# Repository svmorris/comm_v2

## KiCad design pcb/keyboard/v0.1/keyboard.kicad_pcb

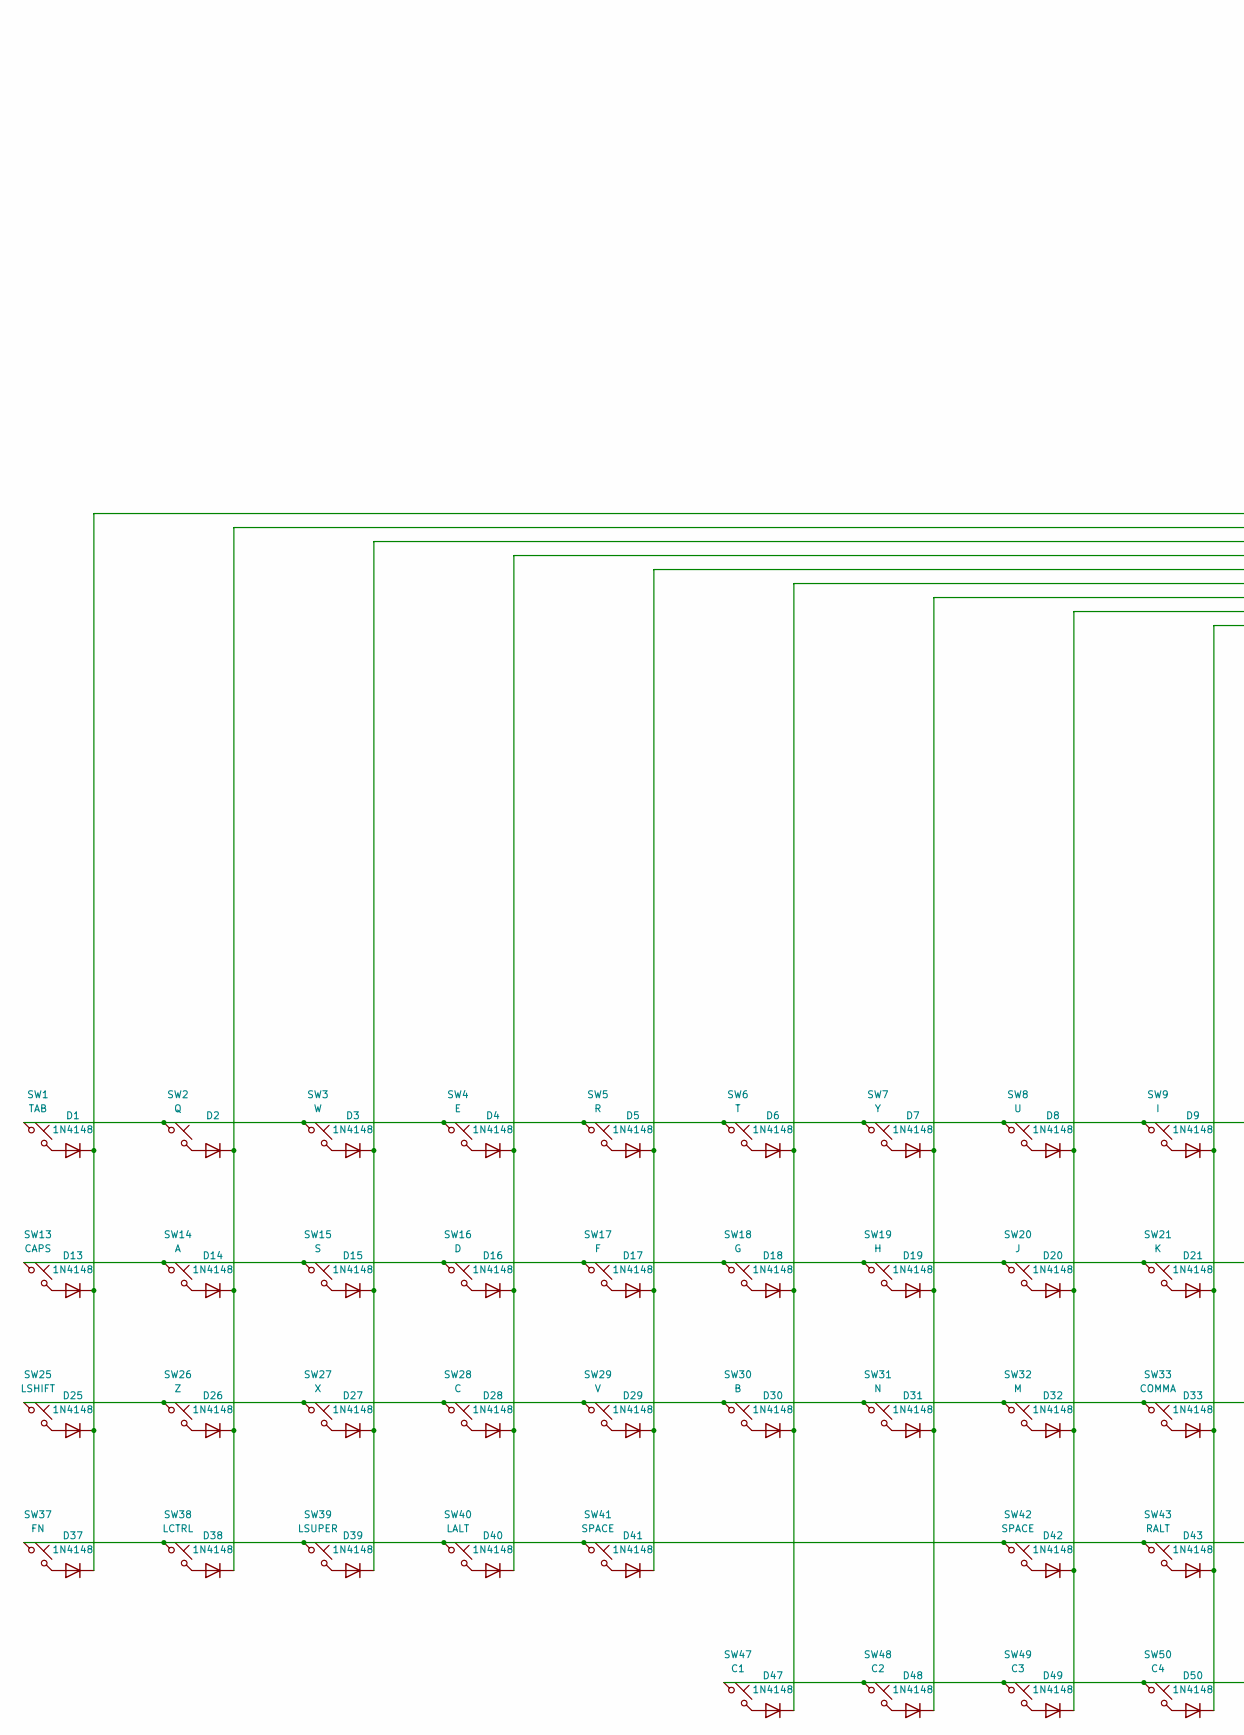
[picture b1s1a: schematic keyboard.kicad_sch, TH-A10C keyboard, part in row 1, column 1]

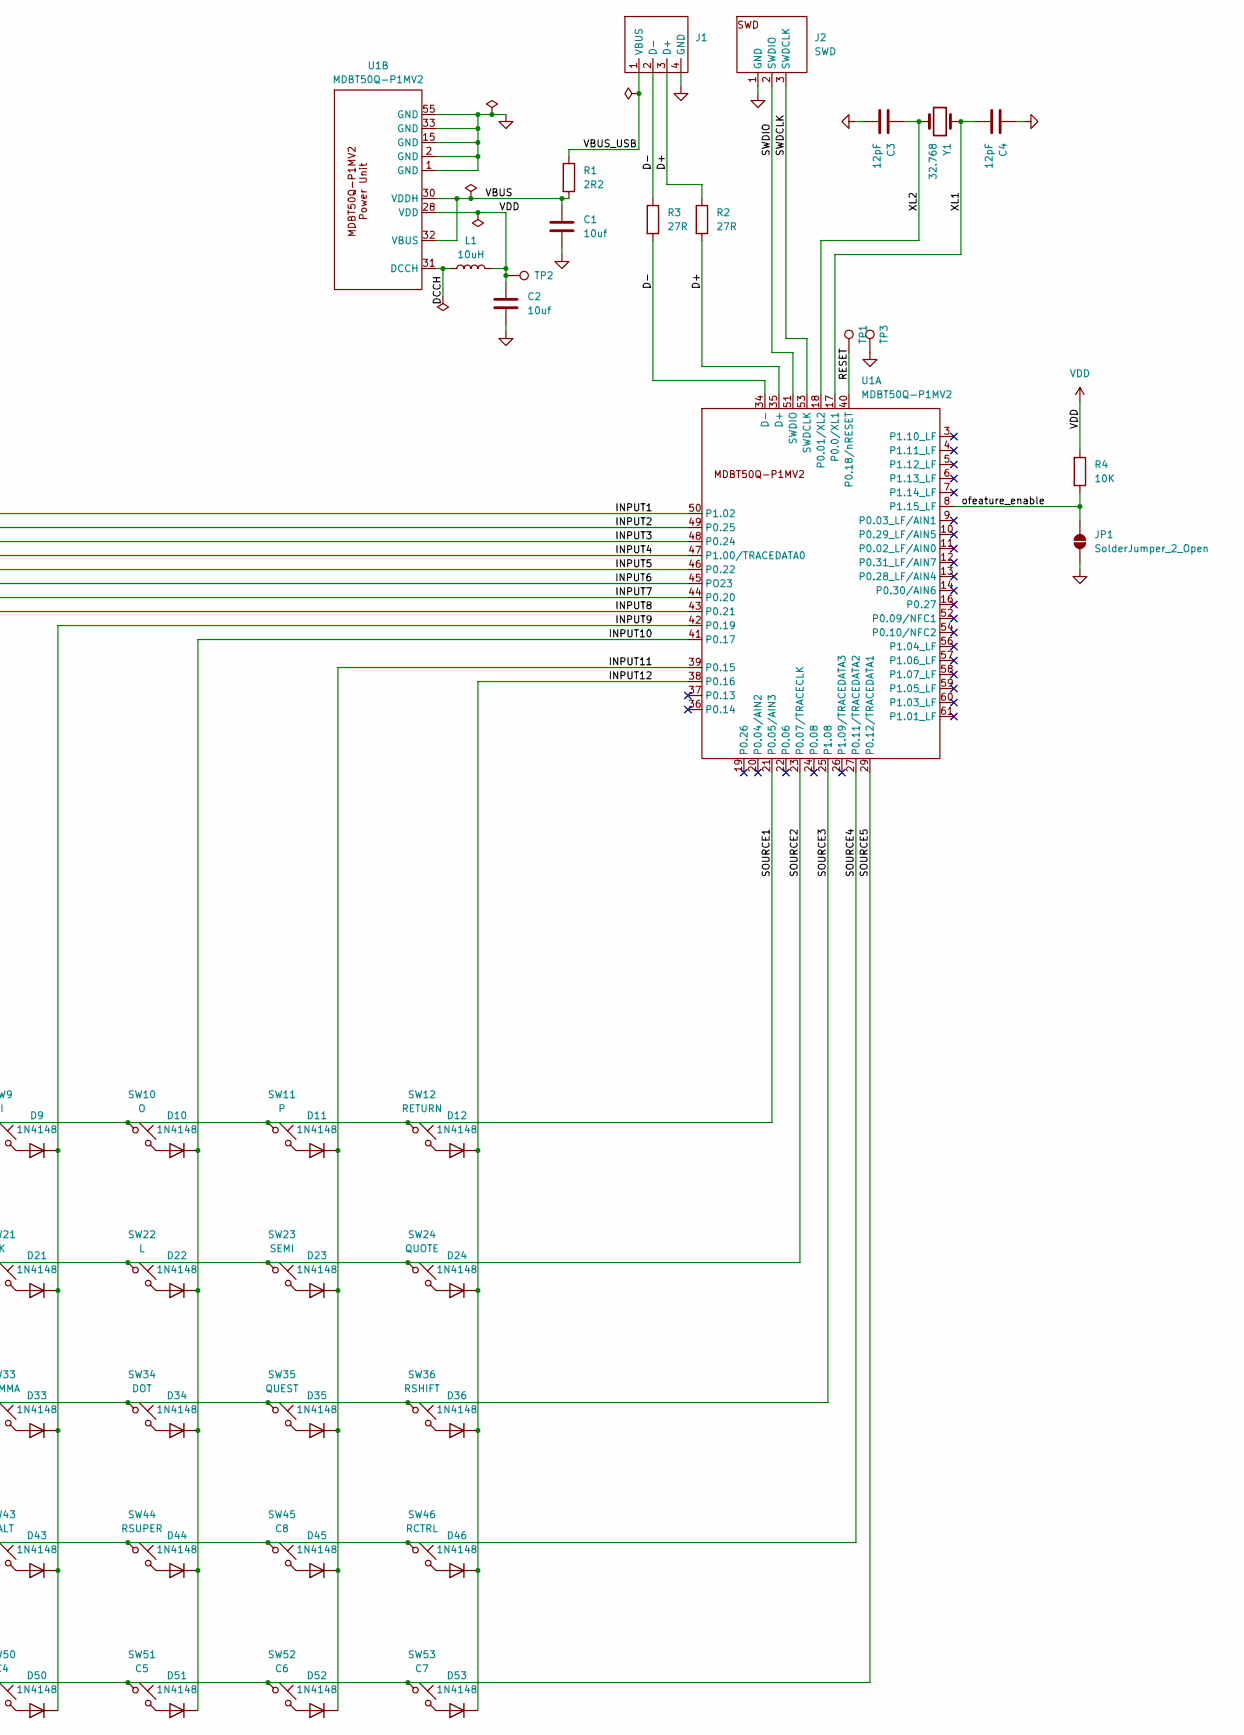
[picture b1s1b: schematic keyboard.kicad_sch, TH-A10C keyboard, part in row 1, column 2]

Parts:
C1, C2: 10uf; C_0805_2012Metric; Mfr. Part no. CL21B106KOQNNNE; LCSC Part no. C95841
C3, C4: 12pF; C_0603_1608Metric; Mfr. Part no. CL10C120JB8NNNC; LCSC Part no. C38523
D1, D2, D3, D4, D5, D6, D7, D8, D9, D10, D11, D12, D13, D14, D15, D16, D17, D18, D19, D20, D21, D22, D23, D24, D25, D26, D27, D28, D29, D30, D31, D32, D33, D34, D35, D36, D37, D38, D39, D40, D41, D42, D43, D44, D45, D46, D47, D48, D49, D50, D51, D52, D53: 1N4148; D_SOD-523; Mfr. Part no. CD4148WTP; LCSC Part no. C30584800
J1: USB2.0; th_pogo_pins_4
J2: SWD; th_pogo_pins_3
JP1: SolderJumper_2_Open; SolderJumper-2_P1.3mm_Open_TrianglePad1.0x1.5mm
L1: 10uH; L_0603_1608Metric; Mfr. Part no SLM1608100MIT; LCSC Part no C2831366
R1: 2R2; R_0603_1608Metric; Mfr. part no. FRC0603F2R20TS; LCSC part no. C2907006
R2, R3: 27R; R_0603_1608Metric; Mfr. part no. 0603WAF270JT5E; LCSC part no. C25190
R4: 10K; R_0603_1608Metric; Mfr. Part no. RC0603FR-0710KL; LCSC Part no. C98220
SW1: TAB; tact_switch_4.5x4.5_PTS647; Mfr. Part no. PTS647SM50SMTR2LFS; LCSC Part no. C2689518
SW2: Q; tact_switch_4.5x4.5_PTS647; Mfr. Part no. PTS647SM50SMTR2LFS; LCSC Part no. C2689518
SW3: W; tact_switch_4.5x4.5_PTS647; Mfr. Part no. PTS647SM50SMTR2LFS; LCSC Part no. C2689518
SW4: E; tact_switch_4.5x4.5_PTS647; Mfr. Part no. PTS647SM50SMTR2LFS; LCSC Part no. C2689518
SW5: R; tact_switch_4.5x4.5_PTS647; Mfr. Part no. PTS647SM50SMTR2LFS; LCSC Part no. C2689518
SW6: T; tact_switch_4.5x4.5_PTS647; Mfr. Part no. PTS647SM50SMTR2LFS; LCSC Part no. C2689518
SW7: Y; tact_switch_4.5x4.5_PTS647; Mfr. Part no. PTS647SM50SMTR2LFS; LCSC Part no. C2689518
SW8: U; tact_switch_4.5x4.5_PTS647; Mfr. Part no. PTS647SM50SMTR2LFS; LCSC Part no. C2689518
SW9: I; tact_switch_4.5x4.5_PTS647; Mfr. Part no. PTS647SM50SMTR2LFS; LCSC Part no. C2689518
SW10: O; tact_switch_4.5x4.5_PTS647; Mfr. Part no. PTS647SM50SMTR2LFS; LCSC Part no. C2689518
SW11: P; tact_switch_4.5x4.5_PTS647; Mfr. Part no. PTS647SM50SMTR2LFS; LCSC Part no. C2689518
SW12: RETURN; tact_switch_4.5x4.5_PTS647; Mfr. Part no. PTS647SM50SMTR2LFS; LCSC Part no. C2689518
SW13: CAPS; tact_switch_4.5x4.5_PTS647; Mfr. Part no. PTS647SM50SMTR2LFS; LCSC Part no. C2689518
SW14: A; tact_switch_4.5x4.5_PTS647; Mfr. Part no. PTS647SM50SMTR2LFS; LCSC Part no. C2689518
SW15: S; tact_switch_4.5x4.5_PTS647; Mfr. Part no. PTS647SM50SMTR2LFS; LCSC Part no. C2689518
SW16: D; tact_switch_4.5x4.5_PTS647; Mfr. Part no. PTS647SM50SMTR2LFS; LCSC Part no. C2689518
SW17: F; tact_switch_4.5x4.5_PTS647; Mfr. Part no. PTS647SM50SMTR2LFS; LCSC Part no. C2689518
SW18: G; tact_switch_4.5x4.5_PTS647; Mfr. Part no. PTS647SM50SMTR2LFS; LCSC Part no. C2689518
SW19: H; tact_switch_4.5x4.5_PTS647; Mfr. Part no. PTS647SM50SMTR2LFS; LCSC Part no. C2689518
SW20: J; tact_switch_4.5x4.5_PTS647; Mfr. Part no. PTS647SM50SMTR2LFS; LCSC Part no. C2689518
SW21: K; tact_switch_4.5x4.5_PTS647; Mfr. Part no. PTS647SM50SMTR2LFS; LCSC Part no. C2689518
SW22: L; tact_switch_4.5x4.5_PTS647; Mfr. Part no. PTS647SM50SMTR2LFS; LCSC Part no. C2689518
SW23: SEMI; tact_switch_4.5x4.5_PTS647; Mfr. Part no. PTS647SM50SMTR2LFS; LCSC Part no. C2689518
SW24: QUOTE; tact_switch_4.5x4.5_PTS647; Mfr. Part no. PTS647SM50SMTR2LFS; LCSC Part no. C2689518
SW25: LSHIFT; tact_switch_4.5x4.5_PTS647; Mfr. Part no. PTS647SM50SMTR2LFS; LCSC Part no. C2689518
SW26: Z; tact_switch_4.5x4.5_PTS647; Mfr. Part no. PTS647SM50SMTR2LFS; LCSC Part no. C2689518
SW27: X; tact_switch_4.5x4.5_PTS647; Mfr. Part no. PTS647SM50SMTR2LFS; LCSC Part no. C2689518
SW28: C; tact_switch_4.5x4.5_PTS647; Mfr. Part no. PTS647SM50SMTR2LFS; LCSC Part no. C2689518
SW29: V; tact_switch_4.5x4.5_PTS647; Mfr. Part no. PTS647SM50SMTR2LFS; LCSC Part no. C2689518
SW30: B; tact_switch_4.5x4.5_PTS647; Mfr. Part no. PTS647SM50SMTR2LFS; LCSC Part no. C2689518
SW31: N; tact_switch_4.5x4.5_PTS647; Mfr. Part no. PTS647SM50SMTR2LFS; LCSC Part no. C2689518
SW32: M; tact_switch_4.5x4.5_PTS647; Mfr. Part no. PTS647SM50SMTR2LFS; LCSC Part no. C2689518
SW33: COMMA; tact_switch_4.5x4.5_PTS647; Mfr. Part no. PTS647SM50SMTR2LFS; LCSC Part no. C2689518
SW34: DOT; tact_switch_4.5x4.5_PTS647; Mfr. Part no. PTS647SM50SMTR2LFS; LCSC Part no. C2689518
SW35: QUEST; tact_switch_4.5x4.5_PTS647; Mfr. Part no. PTS647SM50SMTR2LFS; LCSC Part no. C2689518
SW36: RSHIFT; tact_switch_4.5x4.5_PTS647; Mfr. Part no. PTS647SM50SMTR2LFS; LCSC Part no. C2689518
SW37: FN; tact_switch_4.5x4.5_PTS647; Mfr. Part no. PTS647SM50SMTR2LFS; LCSC Part no. C2689518
SW38: LCTRL; tact_switch_4.5x4.5_PTS647; Mfr. Part no. PTS647SM50SMTR2LFS; LCSC Part no. C2689518
SW39: LSUPER; tact_switch_4.5x4.5_PTS647; Mfr. Part no. PTS647SM50SMTR2LFS; LCSC Part no. C2689518
SW40: LALT; tact_switch_4.5x4.5_PTS647; Mfr. Part no. PTS647SM50SMTR2LFS; LCSC Part no. C2689518
SW41, SW42: SPACE; tact_switch_4.5x4.5_PTS647; Mfr. Part no. PTS647SM50SMTR2LFS; LCSC Part no. C2689518
SW43: RALT; tact_switch_4.5x4.5_PTS647; Mfr. Part no. PTS647SM50SMTR2LFS; LCSC Part no. C2689518
SW44: RSUPER; tact_switch_4.5x4.5_PTS647; Mfr. Part no. PTS647SM50SMTR2LFS; LCSC Part no. C2689518
SW45: C8; tact_switch_4.5x4.5_PTS647; Mfr. Part no. PTS647SM50SMTR2LFS; LCSC Part no. C2689518
SW46: RCTRL; tact_switch_4.5x4.5_PTS647; Mfr. Part no. PTS647SM50SMTR2LFS; LCSC Part no. C2689518
SW47: C1; tact_switch_4.5x4.5_PTS647; Mfr. Part no. PTS647SM50SMTR2LFS; LCSC Part no. C2689518
SW48: C2; tact_switch_4.5x4.5_PTS647; Mfr. Part no. PTS647SM50SMTR2LFS; LCSC Part no. C2689518
SW49: C3; tact_switch_4.5x4.5_PTS647; Mfr. Part no. PTS647SM50SMTR2LFS; LCSC Part no. C2689518
SW50: C4; tact_switch_4.5x4.5_PTS647; Mfr. Part no. PTS647SM50SMTR2LFS; LCSC Part no. C2689518
SW51: C5; tact_switch_4.5x4.5_PTS647; Mfr. Part no. PTS647SM50SMTR2LFS; LCSC Part no. C2689518
SW52: C6; tact_switch_4.5x4.5_PTS647; Mfr. Part no. PTS647SM50SMTR2LFS; LCSC Part no. C2689518
SW53: C7; tact_switch_4.5x4.5_PTS647; Mfr. Part no. PTS647SM50SMTR2LFS; LCSC Part no. C2689518
TP1, TP2, TP3: TestPoint; TestPoint_Pad_D2.0mm
U1: MDBT50Q-P1MV2; TH_MDBT50Q-P1MV2; Mfr Part no. MDBT50Q-P1MV2; LCSC Part no. C5119772
Y1: 32.768; Crystal_SMD_3215-2Pin_3.2x1.5mm; Mfr. Part no. Q13FC13500003; LCSC Part no. C99010

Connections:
/D+: J1.3 (D+), R2.1, R2.2, U1.35 (D+)
/D-: J1.2 (D-), R3.1, R3.2, U1.34 (D-)
/DCCH: L1.1, U1.31 (DCCH)
/INPUT1: D1.1 (K), D13.1 (K), D25.1 (K), D37.1 (K), U1.50 (P1.02)
/INPUT2: D2.1 (K), D14.1 (K), D26.1 (K), D38.1 (K), U1.49 (P0.25)
/INPUT3: D3.1 (K), D15.1 (K), D27.1 (K), D39.1 (K), U1.48 (P0.24)
/INPUT4: D4.1 (K), D16.1 (K), D28.1 (K), D40.1 (K), U1.47 (P1.00/TRACEDATA0)
/INPUT5: D5.1 (K), D17.1 (K), D29.1 (K), D41.1 (K), U1.46 (P0.22)
/INPUT6: D6.1 (K), D18.1 (K), D30.1 (K), D47.1 (K), U1.45 (PO23)
/INPUT7: D7.1 (K), D19.1 (K), D31.1 (K), D48.1 (K), U1.44 (P0.20)
/INPUT8: D8.1 (K), D20.1 (K), D32.1 (K), D42.1 (K), D49.1 (K), U1.43 (P0.21)
/INPUT9: D9.1 (K), D21.1 (K), D33.1 (K), D43.1 (K), D50.1 (K), U1.42 (P0.19)
/INPUT10: D10.1 (K), D22.1 (K), D34.1 (K), D44.1 (K), D51.1 (K), U1.41 (P0.17)
/INPUT11: D11.1 (K), D23.1 (K), D35.1 (K), D45.1 (K), D52.1 (K), U1.39 (P0.15)
/INPUT12: D12.1 (K), D24.1 (K), D36.1 (K), D46.1 (K), D53.1 (K), U1.38 (P0.16)
/RESET: TP1.1, U1.40 (P0.18/nRESET)
/SOURCE1: SW1.1, SW2.1, SW3.1, SW4.1, SW5.1, SW6.1, SW7.1, SW8.1, SW9.1, SW10.1, SW11.1, SW12.1, U1.21 (P0.05/AIN3)
/SOURCE2: SW13.1, SW14.1, SW15.1, SW16.1, SW17.1, SW18.1, SW19.1, SW20.1, SW21.1, SW22.1, SW23.1, SW24.1, U1.23 (P0.07/TRACECLK)
/SOURCE3: SW25.1, SW26.1, SW27.1, SW28.1, SW29.1, SW30.1, SW31.1, SW32.1, SW33.1, SW34.1, SW35.1, SW36.1, U1.25 (P1.08)
/SOURCE4: SW37.1, SW38.1, SW39.1, SW40.1, SW41.1, SW42.1, SW43.1, SW44.1, SW45.1, SW46.1, U1.27 (P0.11/TRACEDATA2)
/SOURCE5: SW47.1, SW48.1, SW49.1, SW50.1, SW51.1, SW52.1, SW53.1, U1.29 (P0.12/TRACEDATA1)
/SWDCLK: J2.3 (SWDCLK), U1.53 (SWDCLK)
/SWDIO: J2.2 (SWDIO), U1.51 (SWDIO)
/VBUS: C1.1, R1.2, U1.30 (VDDH), U1.32 (VBUS)
/VBUS_USB: J1.1 (VBUS), R1.1
/XL1: C4.1, U1.17 (P0.0/XL1), Y1.1
/XL2: C3.2, U1.18 (P0.01/XL2), Y1.2
/ofeature_enable: JP1.2 (B), R4.2, U1.8 (P1.15_LF)
GND: C1.2, C2.2, C3.1, C4.2, J1.4 (GND), J2.1 (GND), JP1.1 (A), TP3.1, U1.1 (GND), U1.2 (GND), U1.15 (GND), U1.33 (GND), U1.55 (GND)
unnamed: D1.2 (A), SW1.2
unnamed: D2.2 (A), SW2.2
unnamed: D3.2 (A), SW3.2
unnamed: D4.2 (A), SW4.2
unnamed: D5.2 (A), SW5.2
unnamed: D6.2 (A), SW6.2
unnamed: D7.2 (A), SW7.2
unnamed: D8.2 (A), SW8.2
unnamed: D9.2 (A), SW9.2
unnamed: D10.2 (A), SW10.2
unnamed: D11.2 (A), SW11.2
unnamed: D12.2 (A), SW12.2
unnamed: D13.2 (A), SW13.2
unnamed: D14.2 (A), SW14.2
unnamed: D15.2 (A), SW15.2
unnamed: D16.2 (A), SW16.2
unnamed: D17.2 (A), SW17.2
unnamed: D18.2 (A), SW18.2
unnamed: D19.2 (A), SW19.2
unnamed: D20.2 (A), SW20.2
unnamed: D21.2 (A), SW21.2
unnamed: D22.2 (A), SW22.2
unnamed: D23.2 (A), SW23.2
unnamed: D24.2 (A), SW24.2
unnamed: D25.2 (A), SW25.2
unnamed: D26.2 (A), SW26.2
unnamed: D27.2 (A), SW27.2
unnamed: D28.2 (A), SW28.2
unnamed: D29.2 (A), SW29.2
unnamed: D30.2 (A), SW30.2
unnamed: D31.2 (A), SW31.2
unnamed: D32.2 (A), SW32.2
unnamed: D33.2 (A), SW33.2
unnamed: D34.2 (A), SW34.2
unnamed: D35.2 (A), SW35.2
unnamed: D36.2 (A), SW36.2
unnamed: D37.2 (A), SW37.2
unnamed: D38.2 (A), SW38.2
unnamed: D39.2 (A), SW39.2
unnamed: D40.2 (A), SW40.2
unnamed: D41.2 (A), SW41.2
unnamed: D42.2 (A), SW42.2
unnamed: D43.2 (A), SW43.2
unnamed: D44.2 (A), SW44.2
unnamed: D45.2 (A), SW45.2
unnamed: D46.2 (A), SW46.2
unnamed: D47.2 (A), SW47.2
unnamed: D48.2 (A), SW48.2
unnamed: D49.2 (A), SW49.2
unnamed: D50.2 (A), SW50.2
unnamed: D51.2 (A), SW51.2
unnamed: D52.2 (A), SW52.2
unnamed: D53.2 (A), SW53.2
VDD: C2.1, L1.2, R4.1, TP2.1, U1.28 (VDD)

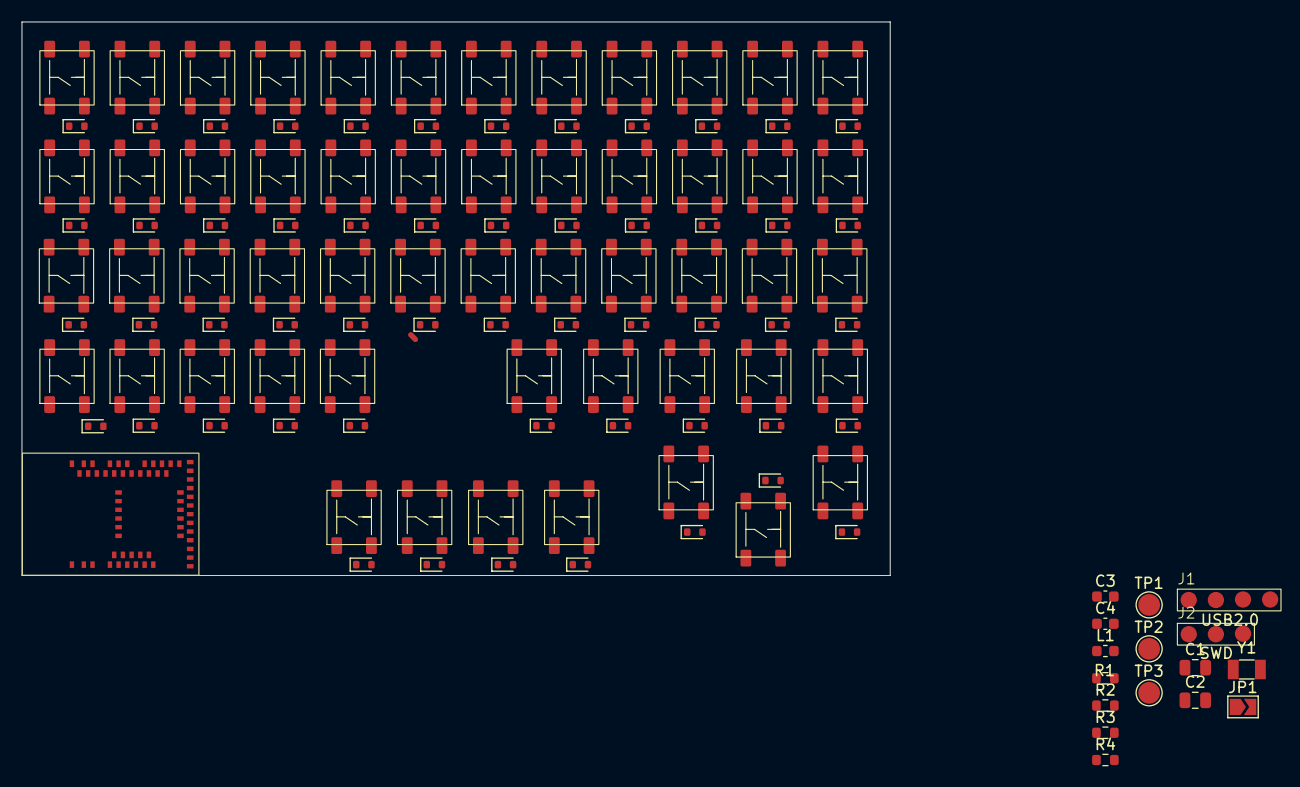
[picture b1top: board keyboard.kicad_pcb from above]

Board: 4 copper layers, 80.0 x 51.0 mm, 123 parts (0 on the bottom side), 83 nets.

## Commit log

2026-02-16 Added zephyr dependency
2026-02-16 Basic USB HID implementation for the keyboard module.
    This commit adds a basic hid keyboard implementation that lines up with
    how the key detection will be done in the code.
2026-02-16 Add keyboard version 0 design files.
    Commit adds the first PCB used for prototyping the keyboard. Named v0
    since this isn't meant to be a functioning keyboard, but rather a board
    with buttons to aid firmware development.
2026-02-17 Quick and dirty keyboard implementation.
    With this commit there is now a functioning keyboard firmware. It can
    do everything a keyboard should, except modifier keys. The current keys
    architecture kinda sucks and should get re-written.
2026-02-18 Finish keyboard v0 design
    This is an early version of the keyboard whose only purpose is to be a
    prototype while I'm working on the firmware for it. Its not to scale, it
    doesn't have an MCU, and its made entirely out of through-hole
    components.
2026-02-20 Clean up keyboard implementation + add mod and fn key.
    The keyboard implementation is now a lot nicer. Its not only more
    efficient, but now has full support for any mod keys.
    Additionally it also includes a custom fn key. This allows for custom
    behaviour defined per key. FN keys can either be part of layer1 where it
    just sends an alternate key, or they can have custom per key functions
    called which are able to do anything.
2026-02-20 Cleaned up some debug messages and usb.c/h functions
2026-02-24 Add initial parts design files
2026-02-26 Rename and update parts
2026-03-02 Switch dp25 -> pin interface
2026-03-06 MCU components complete.
    Only keyboard components and layout to go.
2026-03-07 Found part numbers for button and diode in the keyboard matrix
2026-03-07 Much improved
2026-03-07 Complete keyboard schematic (hopefully)
    Footprints have not been assigned to the keys or the main pcb yet
2026-03-09 Fix incorrect inductor label. 4.7uh -> 10uh
2026-03-10 Labels :)
2026-03-12 Footprints for the two pogo pads
2026-03-12 Footprint for the NRF module!
    Finally I think this means I am done with footprints. Only layout and 3d
    models to go.
2026-03-14 Initial keys layout
    Not sure if this is how we want it yet. Will have to test out without
    the silkscreen key labels if it might give some more space
2026-03-14 Rough layout
2026-03-15 Initial body plan for v3
2026-03-20 New layout again. Also 7 macro keys now to fill the space
2026-03-21 Revert to smaller keyboard, fix a few geometries
